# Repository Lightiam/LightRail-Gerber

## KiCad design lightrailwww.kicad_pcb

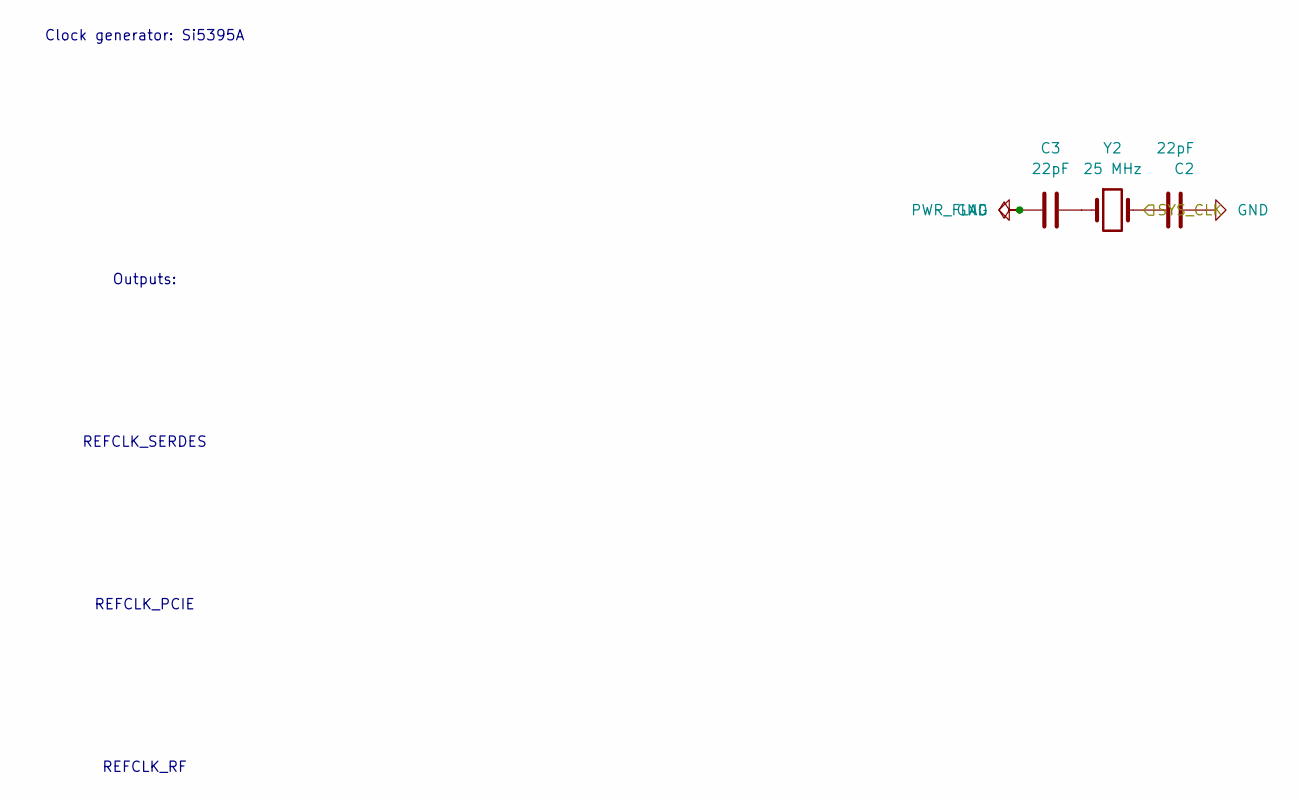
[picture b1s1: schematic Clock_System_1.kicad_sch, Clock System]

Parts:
C2, C3: 22pF; C_0402_1005Metric
Y2: 25 MHz; Crystal_SMD_3215-2Pin_3.2x1.5mm

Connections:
/Clock_System/SYS_CLK: C2.1, Y2.2; also elsewhere on the board
GND: C2.2, C3.2; also elsewhere on the board
unnamed: C3.1, Y2.1

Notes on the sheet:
REFCLK_RF
Clock generator: Si5395A
Outputs:
REFCLK_SERDES
REFCLK_PCIE

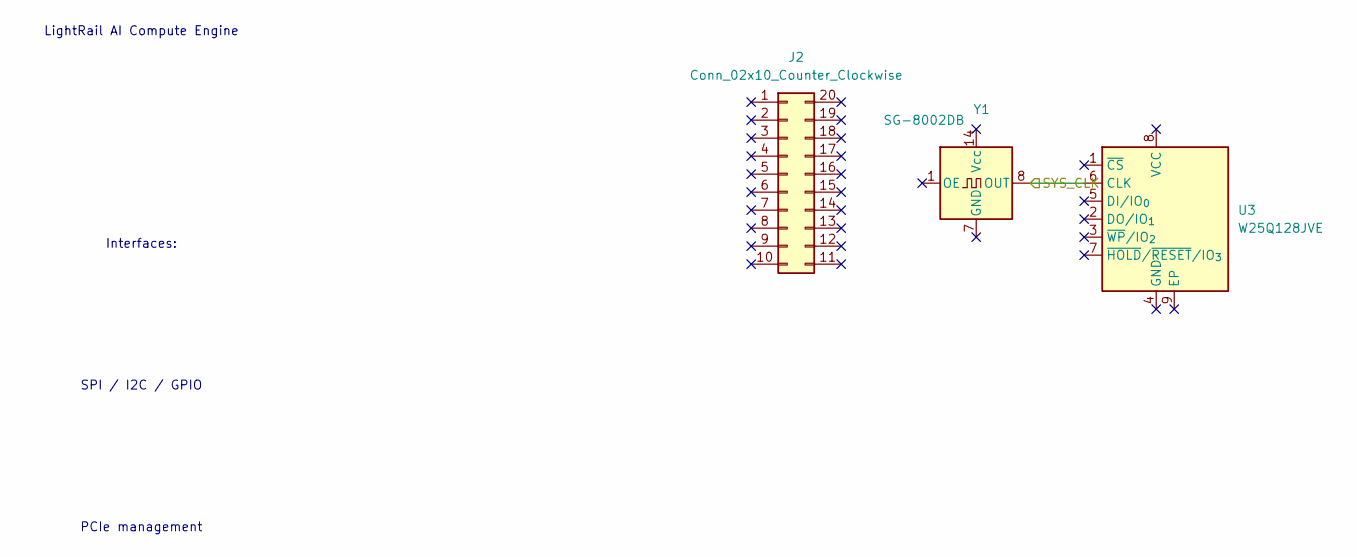
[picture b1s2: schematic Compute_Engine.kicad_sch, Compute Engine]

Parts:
J2: Conn_02x10_Counter_Clockwise; PinHeader_2x10_P2.54mm_Vertical
U3: W25Q128JVE; WSON-8-1EP_8x6mm_P1.27mm_EP3.4x4.3mm
Y1: SG-8002DB; Oscillator_SeikoEpson_SG-8002DB

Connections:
/Clock_System/SYS_CLK: U3.6 (CLK), Y1.8 (OUT); also elsewhere on the board

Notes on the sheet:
LightRail AI Compute Engine
SPI / I2C / GPIO
Interfaces:
PCIe management

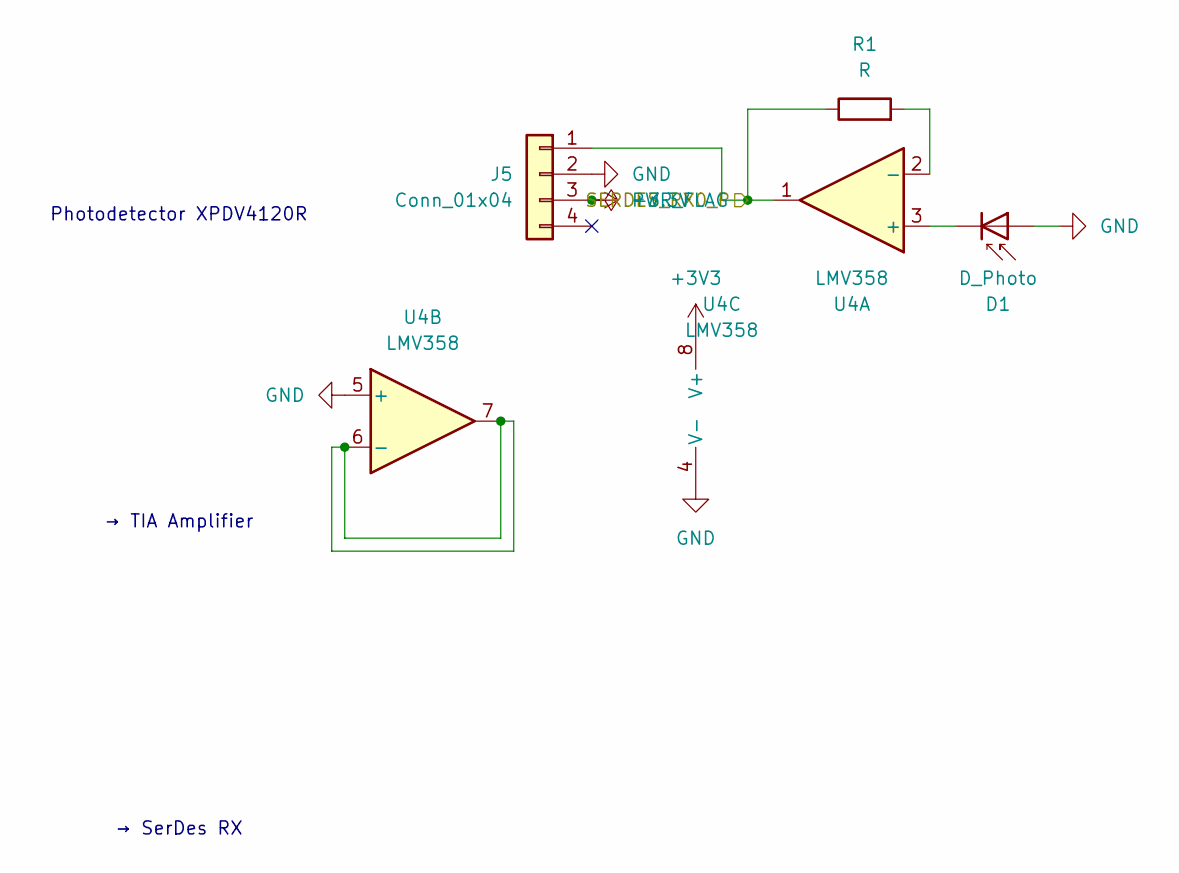
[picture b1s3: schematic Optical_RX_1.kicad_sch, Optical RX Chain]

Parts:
D1: D_Photo; D_SOD-323
J5: Conn_01x04; PinHeader_1x04_P2.54mm_Vertical
R1: R; R_0402_1005Metric
U4: LMV358; SOIC-8_3.9x4.9mm_P1.27mm

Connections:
+3.3V: J5.3
+3V3: U4.8 (V+); also elsewhere on the board
/Optical_RX/SERDES_RX0_P: J5.1, R1.1, U4.1; also elsewhere on the board
GND: D1.2 (A), J5.2, U4.4 (V-), U4.5 (+); also elsewhere on the board
unnamed: D1.1 (K), U4.3 (+)
unnamed: R1.2, U4.2 (-)
unnamed: U4.6 (-), U4.7

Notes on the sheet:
→ TIA Amplifier
→ SerDes RX
Photodetector XPDV4120R

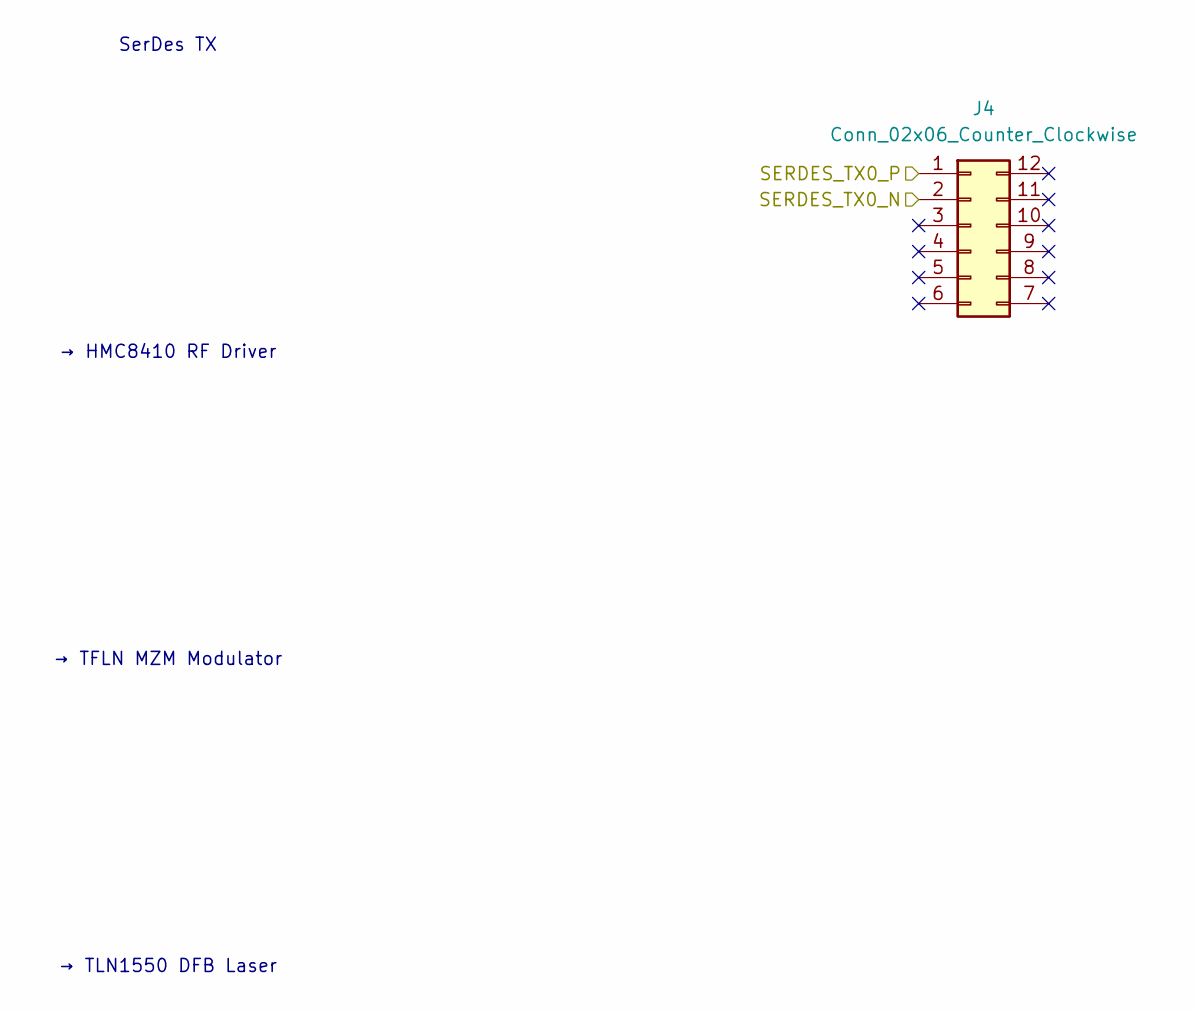
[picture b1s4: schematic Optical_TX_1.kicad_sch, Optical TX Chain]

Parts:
J4: Conn_02x06_Counter_Clockwise; PinHeader_2x06_P2.54mm_Vertical

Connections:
/Optical_TX/SERDES_TX0_N: J4.2; also elsewhere on the board
/Optical_TX/SERDES_TX0_P: J4.1; also elsewhere on the board

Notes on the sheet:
→ TFLN MZM Modulator
→ HMC8410 RF Driver
→ TLN1550 DFB Laser
SerDes TX

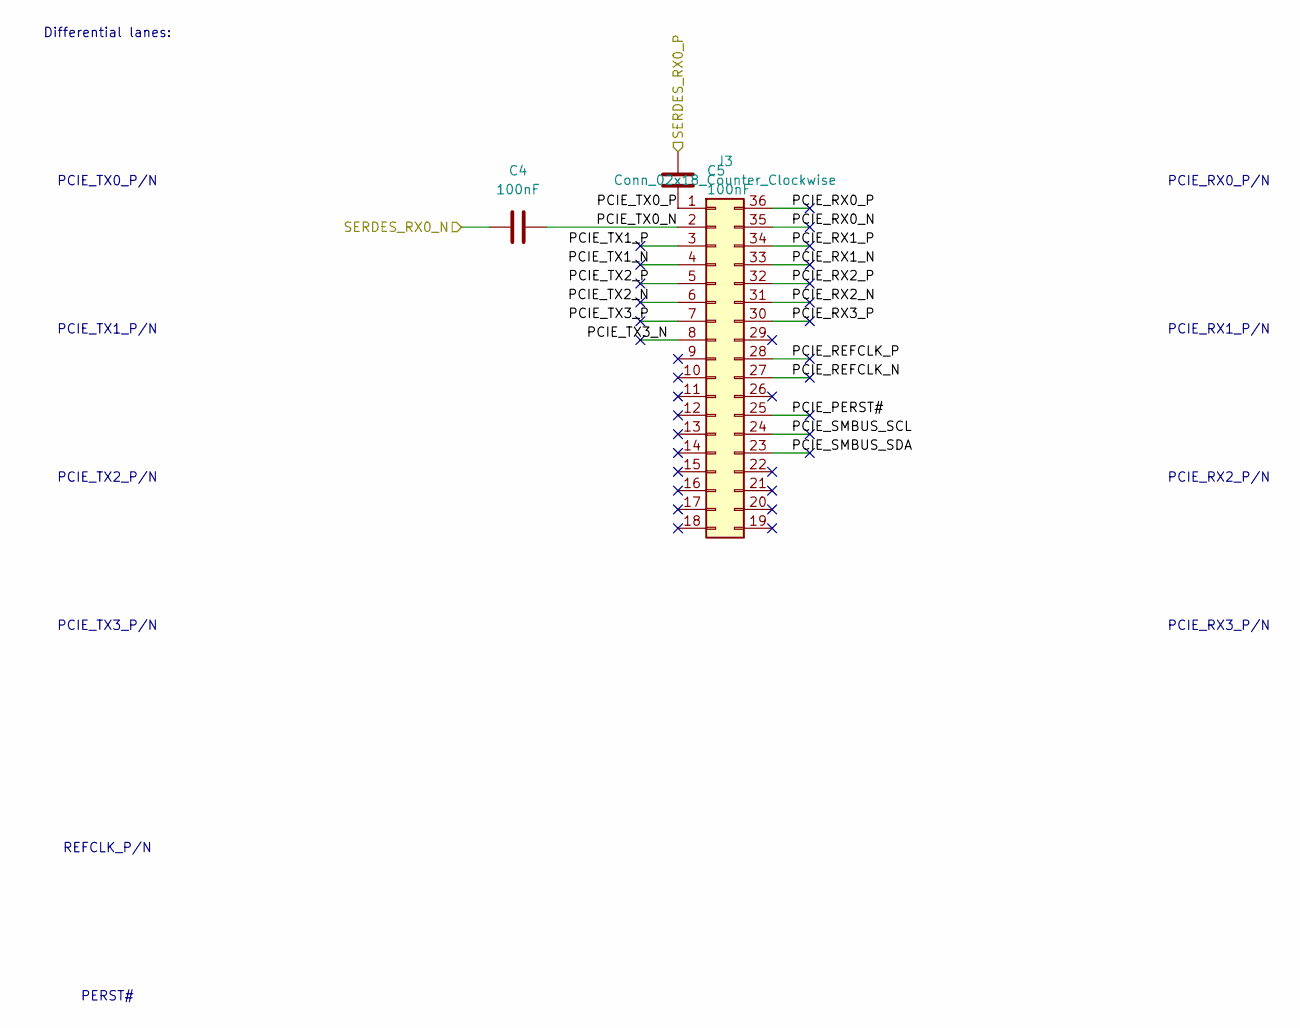
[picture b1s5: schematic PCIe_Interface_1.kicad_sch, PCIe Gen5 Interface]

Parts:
C4: 100nF; C_0402_1005Metric
C5: 100nF; C_0603_1608Metric
J3: Conn_02x18_Counter_Clockwise; PinHeader_2x18_P2.54mm_Vertical

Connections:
/Optical_RX/SERDES_RX0_P: C5.1; also elsewhere on the board
/PCIe_Interface/PCIE_PERST#: J3.25
/PCIe_Interface/PCIE_REFCLK_N: J3.27
/PCIe_Interface/PCIE_REFCLK_P: J3.28
/PCIe_Interface/PCIE_RX0_N: J3.35
/PCIe_Interface/PCIE_RX0_P: J3.36
/PCIe_Interface/PCIE_RX1_N: J3.33
/PCIe_Interface/PCIE_RX1_P: J3.34
/PCIe_Interface/PCIE_RX2_N: J3.31
/PCIe_Interface/PCIE_RX2_P: J3.32
/PCIe_Interface/PCIE_RX3_P: J3.30
/PCIe_Interface/PCIE_SMBUS_SCL: J3.24
/PCIe_Interface/PCIE_SMBUS_SDA: J3.23
/PCIe_Interface/PCIE_TX0_N: C4.2, J3.2
/PCIe_Interface/PCIE_TX0_P: C5.2, J3.1
/PCIe_Interface/PCIE_TX1_N: J3.4
/PCIe_Interface/PCIE_TX1_P: J3.3
/PCIe_Interface/PCIE_TX2_N: J3.6
/PCIe_Interface/PCIE_TX2_P: J3.5
/PCIe_Interface/PCIE_TX3_N: J3.8
/PCIe_Interface/PCIE_TX3_P: J3.7
/PCIe_Interface/SERDES_RX0_N: C4.1; also elsewhere on the board

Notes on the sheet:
PCIE_TX3_P/N
PCIE_TX1_P/N
PCIE_RX3_P/N
PERST#
PCIE_TX0_P/N
REFCLK_P/N
PCIE_RX2_P/N
PCIE_TX2_P/N
Differential lanes:
PCIE_RX1_P/N
PCIE_RX0_P/N

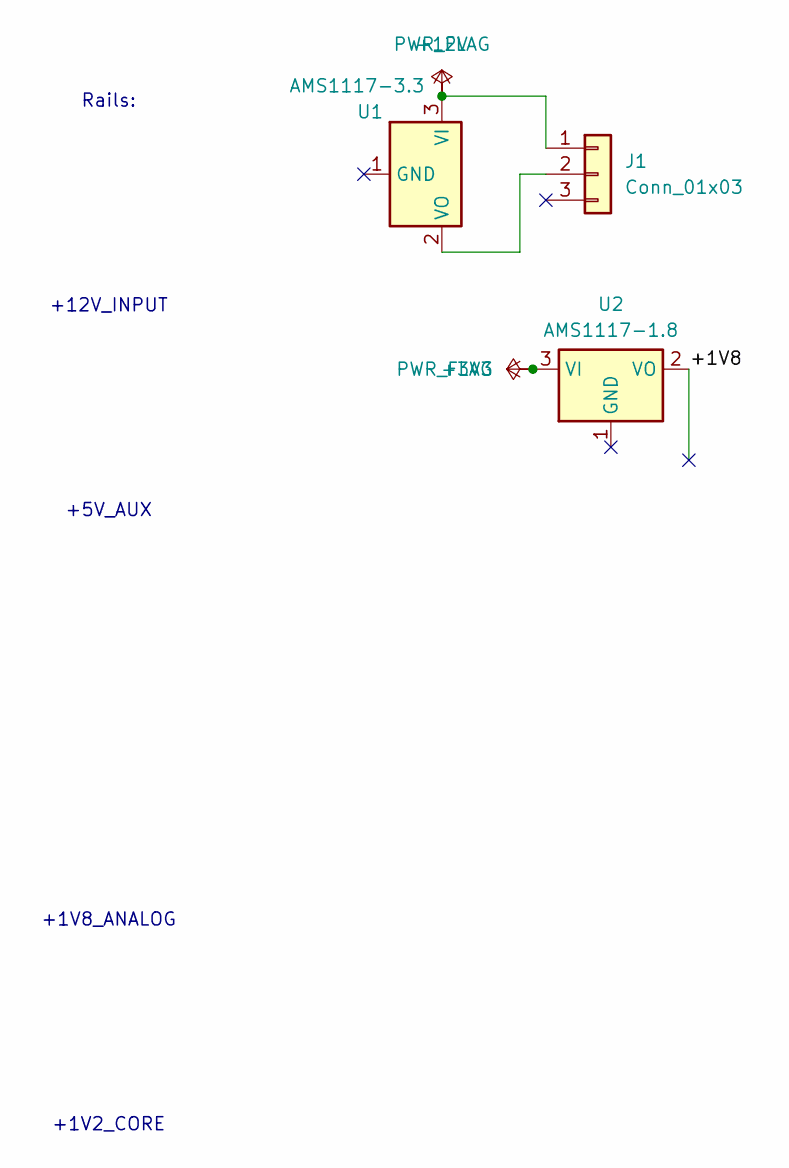
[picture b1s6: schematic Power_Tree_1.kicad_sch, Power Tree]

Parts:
J1: Conn_01x03; FanPinHeader_1x03_P2.54mm_Vertical
U1: AMS1117-3.3; SOT-223-3_TabPin2
U2: AMS1117-1.8; SOT-223-3_TabPin2

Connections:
+3V3: U2.3 (VI); also elsewhere on the board
+12V: J1.1, U1.3 (VI)
/Power_Tree/+1V8: U2.2 (VO)
/Power_Tree/+1V8_1: U2.2 (VO)
unnamed: J1.2, U1.2 (VO)

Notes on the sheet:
+12V_INPUT
Rails:
+5V_AUX
+1V8_ANALOG
+1V2_CORE

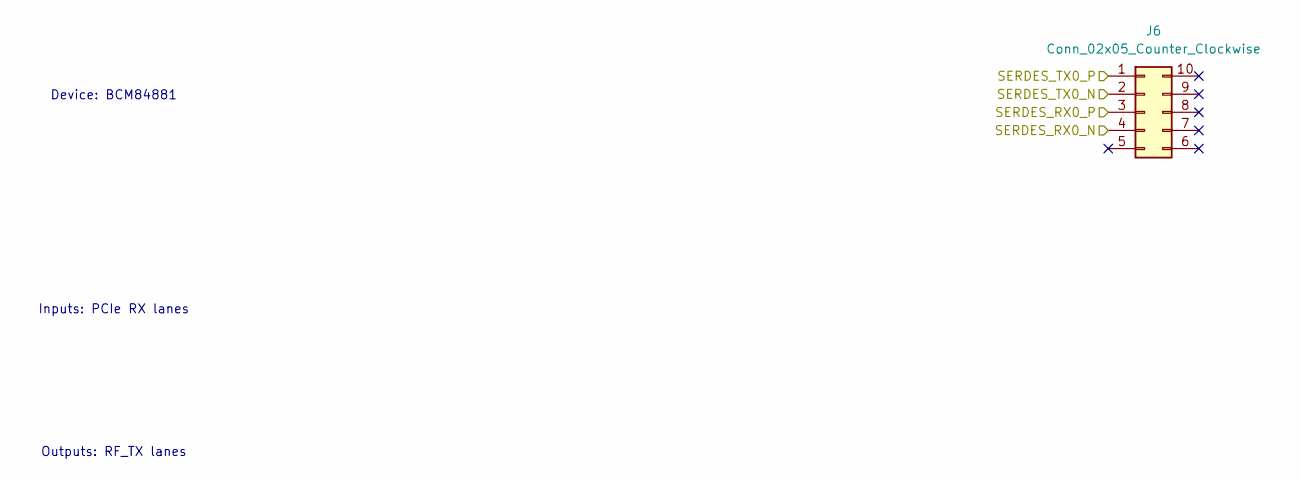
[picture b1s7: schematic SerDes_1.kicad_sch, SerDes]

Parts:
J6: Conn_02x05_Counter_Clockwise; PinHeader_2x05_P2.54mm_Vertical

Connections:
/Optical_RX/SERDES_RX0_P: J6.3; also elsewhere on the board
/Optical_TX/SERDES_TX0_N: J6.2; also elsewhere on the board
/Optical_TX/SERDES_TX0_P: J6.1; also elsewhere on the board
/PCIe_Interface/SERDES_RX0_N: J6.4; also elsewhere on the board

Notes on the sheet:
Outputs: RF_TX lanes
Device: BCM84881
Inputs: PCIe RX lanes

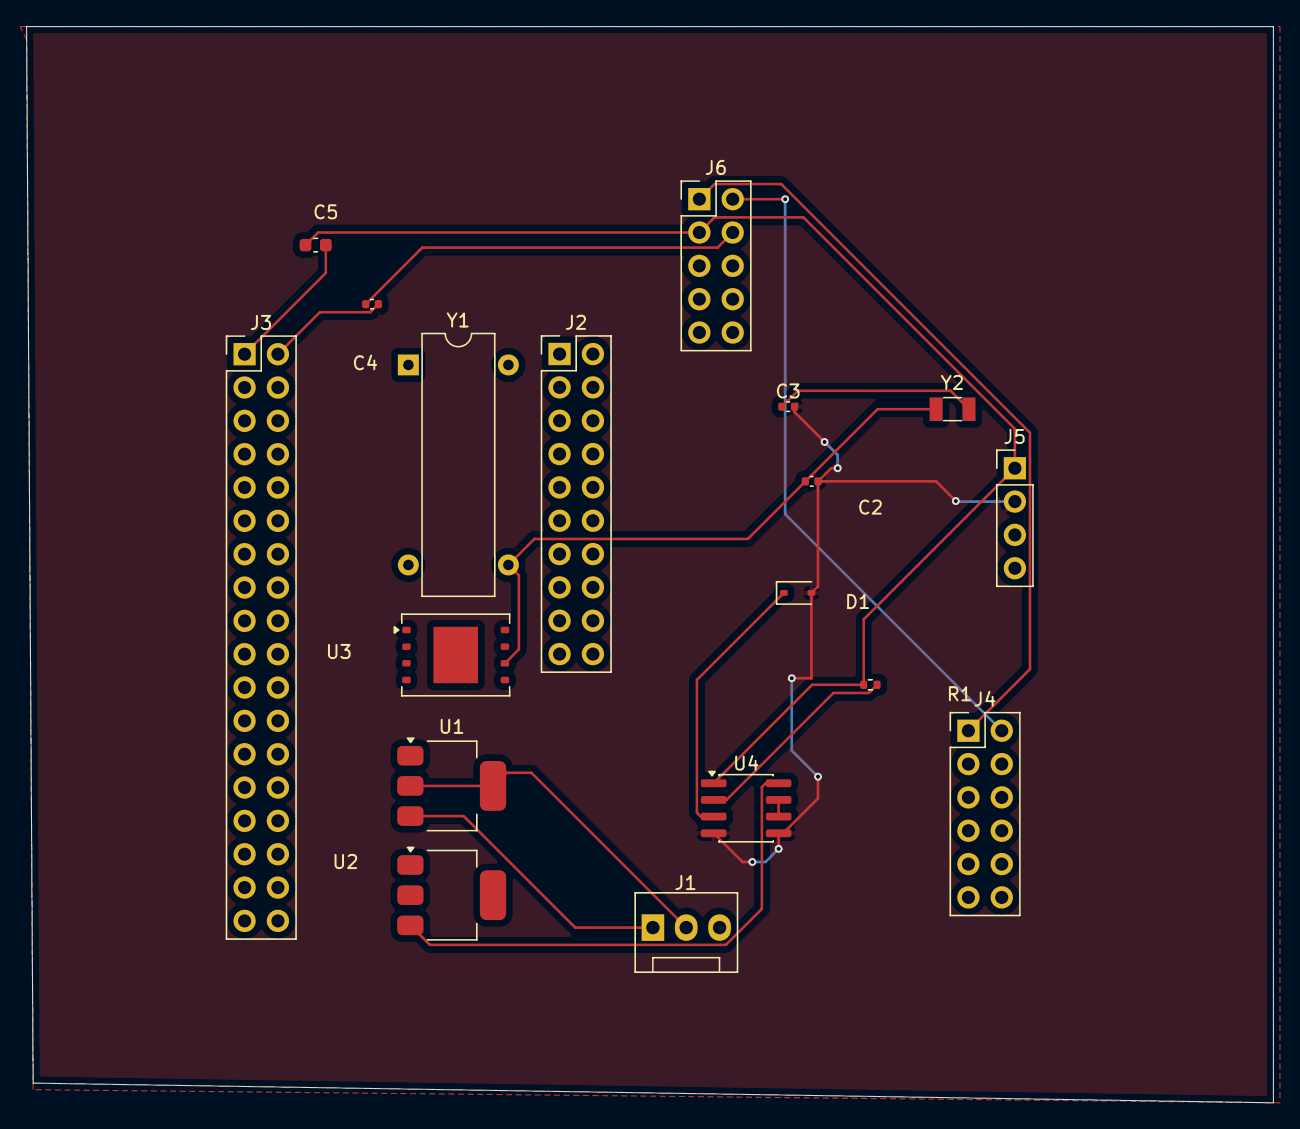
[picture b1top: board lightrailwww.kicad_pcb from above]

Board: 6 copper layers, 95.0 x 82.0 mm, 18 parts (0 on the bottom side), 15 nets.

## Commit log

2026-03-17 LightRail AI files upload
2026-03-17 Fix shorts by refilling copper zones and generating new gerbers
2026-03-17 Update PCB to 16-layer stackup and add inner layer copper routing
2026-03-18 Update PCB stackup to 6 copper layers as requested by fab
2026-03-18 Revert "Update PCB stackup to 6 copper layers as requested by fab"
    This reverts commit 9de2d115b8448442437ad79354c111fe7e6ef276.
2026-03-18 Ensure 16 inner layers have distinct routing and planes to avoid fab rejection
2026-03-18 Finalize distinct 6-layer stackup (Top, In1-4, Bottom) and remove all >In4_Cu layers
2026-03-18 Remove dummy stray traces from In3 and In4
2026-03-18 Absolutely remove stray traces from all inner layers; rename final zip to lightrail_6layer_final.zip
